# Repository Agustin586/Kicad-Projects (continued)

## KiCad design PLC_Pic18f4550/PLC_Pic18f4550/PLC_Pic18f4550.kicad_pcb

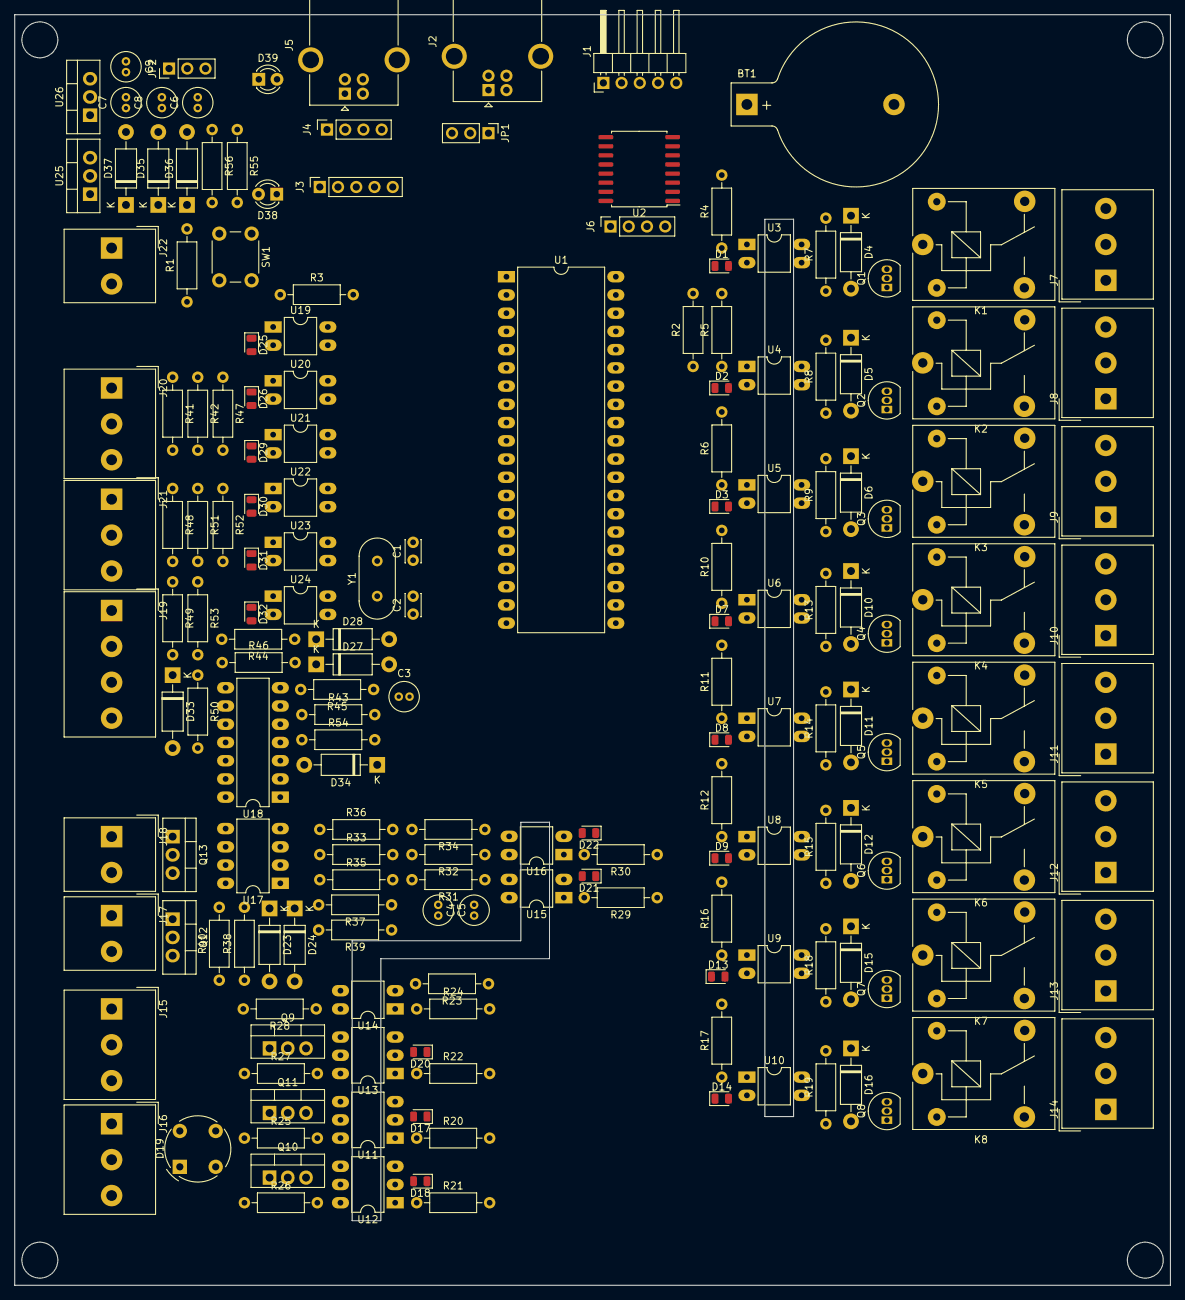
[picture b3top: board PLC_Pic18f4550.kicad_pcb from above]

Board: 2 copper layers, 161.0 x 177.0 mm, 178 parts (0 on the bottom side), 166 nets, no tracks yet.

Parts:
BT1: Battery_Cell; BatteryHolder_Keystone_103_1x20mm
C1, C2: C; C_Disc_D3.0mm_W2.0mm_P2.50mm
C3, C4, C5, C6, C7, C8, C9: C; C_Radial_D4.0mm_H7.0mm_P1.50mm
D1, D2, D3, D7, D8, D9, D13, D14, D17, D18, D20, D21, D22, D25, D26, D29, D30, D31, D32: LED; LED_0805_2012Metric
D4, D5, D6, D10, D11, D12, D15, D16, D23, D24, D35, D36, D37: 1N4007; D_DO-41_SOD81_P10.16mm_Horizontal
D19: D_Bridge_+A-A; Diode_Bridge_Round_D9.0mm
D27, D28, D33, D34: 1N47xxA; D_DO-41_SOD81_P10.16mm_Horizontal
D38, D39: LED; LED_D3.0mm
J1: Conn_01x05_Male; PinHeader_1x05_P2.54mm_Horizontal
J2, J5: USB_B; USB_B_OST_USB-B1HSxx_Horizontal
J3: Conn_01x05_Female; PinSocket_1x05_P2.54mm_Vertical
J4: Conn_01x04_Female; PinSocket_1x04_P2.54mm_Vertical
J6: Lcd_I2C; PinSocket_1x04_P2.54mm_Vertical
J7: SalidaRele0; Altech_AK300_1x03_P5.00mm_45-Degree
J8: SalidaRele1; Altech_AK300_1x03_P5.00mm_45-Degree
J9: SalidaRele2; Altech_AK300_1x03_P5.00mm_45-Degree
J10: SalidaRele3; Altech_AK300_1x03_P5.00mm_45-Degree
J11: SalidaRele4; Altech_AK300_1x03_P5.00mm_45-Degree
J12: SalidaRele5; Altech_AK300_1x03_P5.00mm_45-Degree
J13: SalidaRele6; Altech_AK300_1x03_P5.00mm_45-Degree
J14, J15, J16, J20, J21: Screw_Terminal_01x03; Altech_AK300_1x03_P5.00mm_45-Degree
J17, J18, J22: Screw_Terminal_01x02; Altech_AK300_1x02_P5.00mm_45-Degree
J19: Screw_Terminal_01x04; Altech_AK300_1x04_P5.00mm_45-Degree
JP1, JP2: Jumper_3_Bridged12; PinHeader_1x03_P2.54mm_Vertical
K1: Relay0; Relay_SPDT_SANYOU_SRD_Series_Form_C
K2: Relay1; Relay_SPDT_SANYOU_SRD_Series_Form_C
K3: Relay2; Relay_SPDT_SANYOU_SRD_Series_Form_C
K4: Relay3; Relay_SPDT_SANYOU_SRD_Series_Form_C
K5: Relay4; Relay_SPDT_SANYOU_SRD_Series_Form_C
K6: Relay5; Relay_SPDT_SANYOU_SRD_Series_Form_C
K7: Relay7; Relay_SPDT_SANYOU_SRD_Series_Form_C
K8: Relay8; Relay_SPDT_SANYOU_SRD_Series_Form_C
Q1, Q2, Q3, Q4, Q5, Q6, Q7, Q8: BC548; TO-92_Inline
Q9, Q10, Q11: BT136-500; TO-220-3_Vertical
Q12, Q13: IRF540N; TO-220-3_Vertical
R1, R2, R3, R4, R5, R6, R7, R8, R9, R10, R11, R12, R13, R14, R15, R16, R17, R18, R19, R20, R21, R22, R23, R24, R25, R26, R27, R28, R29, R30, R31, R32, R33, R34, R35, R36, R37, R38, R39, R40, R41, R42, R43, R44, R45, R46, R47, R48, R49, R50, R51, R52, R53, R54, R55, R56: R; R_Axial_DIN0207_L6.3mm_D2.5mm_P10.16mm_Horizontal
SW1: SW_Push; SW_PUSH_6mm
U1: PIC18F4550-IP; DIP-40_W15.24mm_LongPads
U2: DS3231M; SOIC-16W_7.5x10.3mm_P1.27mm
U3, U4, U5, U6, U7, U8, U9, U10, U14, U15, U16, U19, U20, U21, U22, U23, U24: PC817; DIP-4_W7.62mm_LongPads
U11, U12, U13: MOC3021M; DIP-6_W7.62mm_LongPads
U17: LM358; DIP-8_W7.62mm_LongPads
U18: LM324A; DIP-14_W7.62mm_LongPads
U25: LM7805_TO220; TO-220-3_Vertical
U26: LM7810_TO220; TO-220-3_Vertical
Y1: Crystal; Crystal_HC18-U_Vertical

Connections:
+5V: D4.1, D5.1, D6.1, D10.1, D11.1, D12.1, D15.1, D16.1, J1.2, J3.5, J6.3, JP2.2, K1.5, K2.5, K3.5, K4.5, K5.5, K6.5, K7.5, K8.5, R1.1, R2.1, R3.1, R28.2, R55.1, U1.11, U1.32, U2.2, U3.4, U4.4, U5.4, U6.4, U7.4, U8.4, U9.4, U10.4, U15.4, U16.4, U19.4, U20.4, U21.4, U22.4, U23.4, U24.4
+10V: C9.1, D23.1, D24.1, R56.1, U18.4, U26.3
+24V: D35.2, D36.2, J22.1, U17.8
/Control/OSC1: C1.1, U1.13, Y1.2
/Control/OSC2: C2.1, U1.14, Y1.1
/Control/RC4: J2.2, U1.23
/Control/RC5: J2.3, U1.24
/Control/RESET: JP1.2, U1.1
/Entradas/A0: J19.1, U18.3
/Entradas/A1: J19.2, U18.5
/Entradas/A2: J19.3, U18.10
/Entradas/A3: J19.4, U18.12
/Entradas/I0: J20.1, R41.2
/Entradas/I1: J20.2, R42.2
/Entradas/I2: J20.3, R47.2
/Entradas/I3: J21.1, R48.2
/Entradas/I4: J21.2, R51.2
/Entradas/I5: J21.3, R52.2
/Salidas/Salida_Reles/Rele1/Relay0: J7.1, K1.3
/Salidas/Salida_Reles/Rele1/Relay1: J7.3, K2.3
/Salidas/Salida_Reles/Rele1/Relay2: J8.2, K3.3
/Salidas/Salida_Reles/Rele1/Relay3: J9.1, K4.3
/Salidas/Salida_Reles/Rele1/Relay4: J10.1, K5.3
/Salidas/Salida_Reles/Rele1/Relay5: J10.3, K6.3
/Salidas/Salida_Reles/Rele1/Relay6: J11.2, K8.3
/Salidas/Salida_Reles/Rele1/Relay7: J12.1, K7.3
/Salidas/Salidas_Mosfet/Salida_Mosfet1: J17.1, Q12.3, R39.2
/Salidas/Salidas_Mosfet/Salida_Mosfet2: J18.1, Q13.3, R40.2
/Salidas/Salidas_Triac/Triac0: J15.1, Q10.1
/Salidas/Salidas_Triac/Triac1: J15.3, Q11.1
/Salidas/Salidas_Triac/Triac2: J16.2, Q9.1
CxC: R28.1, U1.35, U14.4
GND: BT1.2, C1.2, C2.2, C3.1, C4.1, C5.1, C6.2, C7.2, C8.2, C9.2, D1.1, D2.1, D3.1, D7.1, D8.1, D9.1, D13.1, D14.1, D17.1, D18.1, D20.1, D21.1, D22.1, D25.1, D26.1, D27.2, D28.2, D29.1, D30.1, D31.1, D32.1, D33.2, D34.2, D38.1, D39.1, J1.3, J2.4, J3.4, J6.4, J17.2, J18.2, J22.2, Q1.3, Q2.3, Q3.3, Q4.3, Q5.3, Q6.3, Q7.3, Q8.3, R33.1, R34.1, R45.1, R46.1, R53.1, R54.1, SW1.1, U1.12, U1.31, U2.5, U2.6, U2.7, U2.8, U2.9, U2.10, U2.11, U2.12, U2.13, U14.3, U17.4, U18.11, U25.2, U26.2
I0.0: U1.37, U19.3
I0.1: U1.38, U20.3
I0.2: J1.5, U1.39, U21.3
I0.3: J1.4, U1.40, U22.3
I0.4: U1.6, U23.3
I0.5: U1.7, U24.3
IA0.0: D27.1, R43.1, R45.2, U1.2
IA0.1: D28.1, R44.1, R46.2, U1.3
IA0.2: D33.1, R49.1, R53.2, U1.4
IA0.3: D34.1, R50.1, R54.2, U1.5
LineaAC1: D19.2, J14.1, K1.1, K2.1, K3.1, K4.1, Q9.2, Q10.2, Q11.2, R25.1, R26.1, R27.1
LineaAC2: D19.4, J7.2, J8.1, J8.3, J9.2, J14.3, J15.2, J16.1, J16.3
LineaDC1: J13.1, K5.1, K6.1, K7.1, K8.1
LineaDC2: J10.2, J11.1, J11.3, J12.2, J13.3
unnamed: BT1.1, U2.14
unnamed: C3.2, U1.18
unnamed: C4.2, R31.2, U17.3
unnamed: C5.2, R32.2, U17.5
unnamed: C6.1, D35.1, D37.1, U25.1
unnamed: C7.1, D36.1, U26.1
unnamed: C8.1, D37.2, JP2.1, U25.3
unnamed: D1.2, U3.2
unnamed: D2.2, U4.2
unnamed: D3.2, U5.2
unnamed: D4.2, K1.2, Q1.1
unnamed: D5.2, K2.2, Q2.1
unnamed: D6.2, K3.2, Q3.1
unnamed: D7.2, U6.2
unnamed: D8.2, U7.2
unnamed: D9.2, U8.2
unnamed: D10.2, K4.2, Q4.1
unnamed: D11.2, K5.2, Q5.1
unnamed: D12.2, K6.2, Q6.1
unnamed: D13.2, U9.2
unnamed: D14.2, U10.2
unnamed: D15.2, K7.2, Q7.1
unnamed: D16.2, K8.2, Q8.1
unnamed: D17.2, U11.2
unnamed: D18.2, U12.2
unnamed: D19.1, R23.2
unnamed: D19.3, U14.2
unnamed: D20.2, U13.2
unnamed: D21.2, U15.2
unnamed: D22.2, U16.2
unnamed: D23.2, Q12.2
unnamed: D24.2, Q13.2
unnamed: D25.2, U19.2
unnamed: D26.2, U20.2
unnamed: D29.2, U21.2
unnamed: D30.2, U22.2
unnamed: D31.2, U23.2
unnamed: D32.2, U24.2
unnamed: D38.2, R55.2
unnamed: D39.2, R56.2
unnamed: J1.1, JP1.1
unnamed: J4.1, J5.4
unnamed: J4.2, J5.3
unnamed: J4.3, J5.2
unnamed: J4.4, J5.1
unnamed: JP1.3, R1.2, SW1.2
unnamed: Q1.2, R7.1
unnamed: Q2.2, R8.1
unnamed: Q3.2, R9.1
unnamed: Q4.2, R13.1
unnamed: Q5.2, R14.1
unnamed: Q6.2, R15.1
unnamed: Q7.2, R18.1
unnamed: Q8.2, R19.1
unnamed: Q9.3, U11.4
unnamed: Q10.3, U12.4
unnamed: Q11.3, U13.4
unnamed: Q12.1, R37.1, R39.1
unnamed: Q13.1, R38.1, R40.1
unnamed: R4.1, U3.1
unnamed: R5.1, U4.1
unnamed: R6.1, U5.1
unnamed: R7.2, U3.3
unnamed: R8.2, U4.3
unnamed: R9.2, U5.3
unnamed: R10.1, U6.1
unnamed: R11.1, U7.1
unnamed: R12.1, U8.1
unnamed: R13.2, U6.3
unnamed: R14.2, U7.3
unnamed: R15.2, U8.3
unnamed: R16.1, U9.1
unnamed: R17.1, U10.1
unnamed: R18.2, U9.3
unnamed: R19.2, U10.3
unnamed: R20.1, U11.1
unnamed: R21.1, U12.1
unnamed: R22.1, U13.1
unnamed: R23.1, R24.2
unnamed: R24.1, U14.1
unnamed: R25.2, U11.6
unnamed: R26.2, U12.6
unnamed: R27.2, U13.6
unnamed: R29.2, U15.1
unnamed: R30.2, U16.1
unnamed: R31.1, U15.3
unnamed: R32.1, U16.3
unnamed: R33.2, R35.2, U17.2
unnamed: R34.2, R36.2, U17.6
unnamed: R35.1, R37.2, U17.1
unnamed: R36.1, R38.2, U17.7
unnamed: R41.1, U19.1
unnamed: R42.1, U20.1
unnamed: R43.2, U18.1, U18.2
unnamed: R44.2, U18.6, U18.7
unnamed: R47.1, U21.1
unnamed: R48.1, U22.1
unnamed: R49.2, U18.8, U18.9
unnamed: R50.2, U18.13, U18.14
unnamed: R51.1, U23.1
unnamed: R52.1, U24.1
Q0.0: R4.2, U1.19
Q0.1: R5.2, U1.20
Q0.2: R6.2, U1.21
Q0.3: R10.2, U1.22
Q0.4: R11.2, U1.27
Q0.5: R12.2, U1.28
Q0.6: R16.2, U1.29
Q0.7: R17.2, U1.30
Q1.0: R21.2, U1.8
Q1.1: R22.2, U1.9
Q1.2: R20.2, U1.10
Q1.3: R29.1, U1.16
Q1.4: R30.1, U1.17
RX: J3.2, U1.26
SCL: J6.1, R3.2, U1.34, U2.16
SDA: J6.2, R2.2, U1.33, U2.15
TX: J3.3, U1.25
VUSB: J2.1, JP2.3

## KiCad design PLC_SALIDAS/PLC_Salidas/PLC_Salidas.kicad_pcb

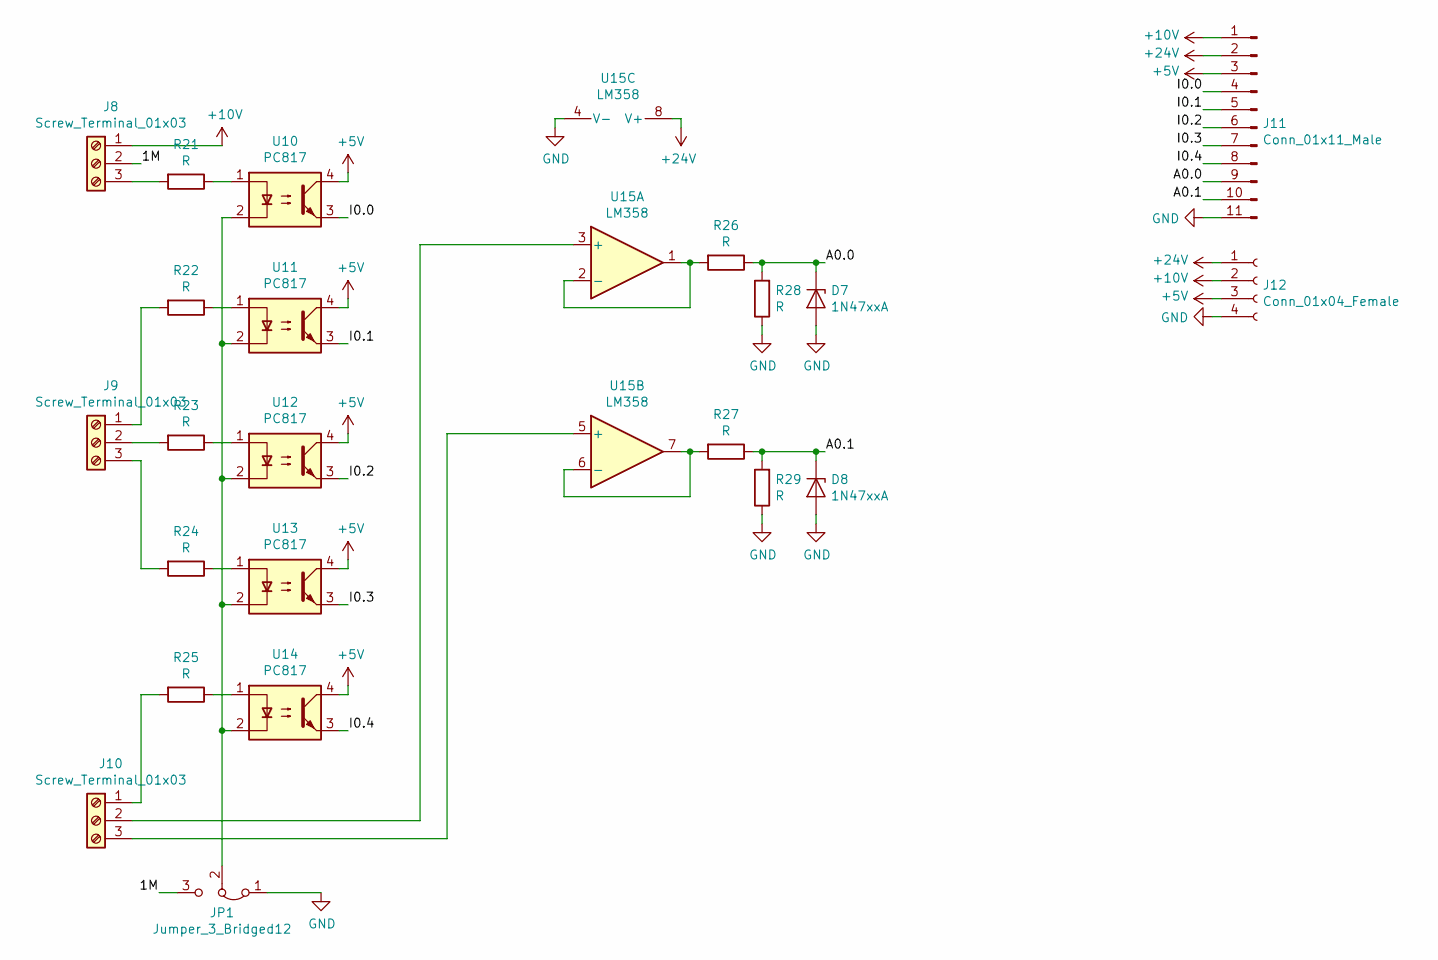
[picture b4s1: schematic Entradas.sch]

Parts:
D7, D8: 1N47xxA; D_DO-41_SOD81_P10.16mm_Horizontal
J8, J9, J10: Screw_Terminal_01x03; TerminalBlock_Phoenix_PT-1,5-3-5.0-H_1x03_P5.00mm_Horizontal
J11: Conn_01x11_Male; PinHeader_1x11_P2.54mm_Vertical
J12: Conn_01x04_Female; PinSocket_1x04_P2.54mm_Vertical
JP1: Jumper_3_Bridged12; PinHeader_1x03_P2.54mm_Vertical
R21, R22, R23, R24, R25, R26, R27, R28, R29: R; R_Axial_DIN0207_L6.3mm_D2.5mm_P10.16mm_Horizontal
U10, U11, U12, U13, U14: PC817; DIP-4_W7.62mm
U15: LM358; DIP-8_W7.62mm_LongPads

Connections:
+5V: J11.3, J12.3, U10.4, U11.4, U12.4, U13.4, U14.4; also elsewhere on the board
+10V: J8.1, J11.1, J12.2
+24V: J11.2, J12.1, U15.8 (V+)
/Entradas/1M: J8.2, JP1.3 (B)
/Entradas/A0.0: D7.1 (K), J11.9, R26.1, R28.2
/Entradas/A0.1: D8.1 (K), J11.10, R27.1, R29.2
/Entradas/I0.0: J11.4, U10.3
/Entradas/I0.1: J11.5, U11.3
/Entradas/I0.2: J11.6, U12.3
/Entradas/I0.3: J11.7, U13.3
/Entradas/I0.4: J11.8, U14.3
GND: D7.2 (A), D8.2 (A), J11.11, J12.4, JP1.1 (A), R28.1, R29.1, U15.4 (V-); also elsewhere on the board
unnamed: J8.3, R21.2
unnamed: J9.1, R22.2
unnamed: J9.2, R23.2
unnamed: J9.3, R24.2
unnamed: J10.1, R25.2
unnamed: J10.2, U15.3 (+)
unnamed: J10.3, U15.5 (+)
unnamed: JP1.2 (C), U10.2, U11.2, U12.2, U13.2, U14.2
unnamed: R21.1, U10.1
unnamed: R22.1, U11.1
unnamed: R23.1, U12.1
unnamed: R24.1, U13.1
unnamed: R25.1, U14.1
unnamed: R26.2, U15.1, U15.2 (-)
unnamed: R27.2, U15.6 (-), U15.7

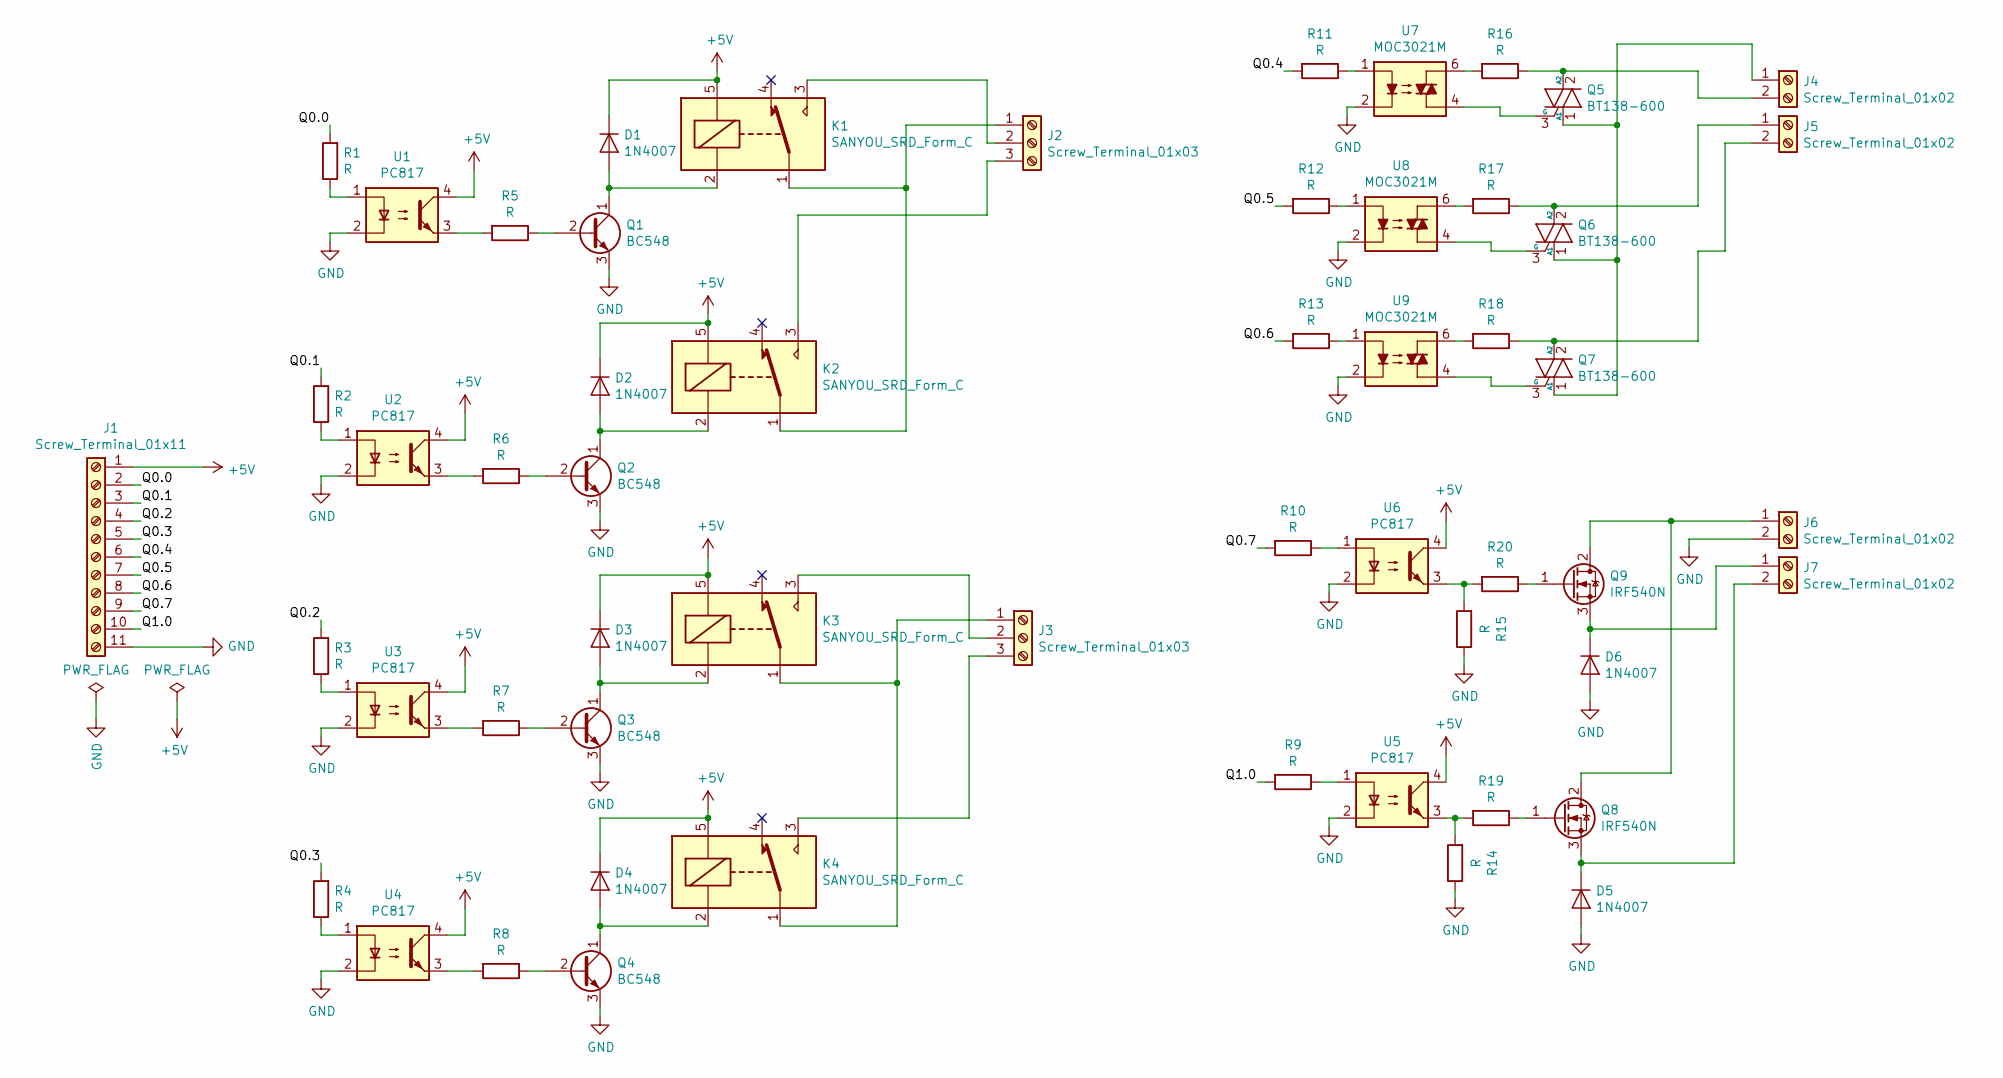
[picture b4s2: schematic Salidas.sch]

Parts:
D1, D2, D3, D4, D5, D6: 1N4007; D_DO-41_SOD81_P10.16mm_Horizontal
J1: Screw_Terminal_01x11; PinHeader_1x11_P2.54mm_Vertical
J2, J3: Screw_Terminal_01x03; TerminalBlock_Phoenix_PT-1,5-3-5.0-H_1x03_P5.00mm_Horizontal
J4, J5, J6, J7: Screw_Terminal_01x02; TerminalBlock_Phoenix_PT-1,5-2-5.0-H_1x02_P5.00mm_Horizontal
K1, K2, K3, K4: SANYOU_SRD_Form_C; Relay_SPDT_SANYOU_SRD_Series_Form_C
Q1, Q2, Q3, Q4: BC548; TO-92_Inline_Wide
Q5, Q6, Q7: BT138-600; TO-220-3_Vertical
Q8, Q9: IRF540N; TO-220-3_Vertical
R1, R2, R3, R4, R5, R6, R7, R8, R9, R10, R11, R12, R13, R14, R15, R16, R17, R18, R19, R20: R; R_Axial_DIN0207_L6.3mm_D2.5mm_P10.16mm_Horizontal
U1, U2, U3, U4: PC817; DIP-4_W7.62mm_LongPads
U5, U6: PC817; DIP-4_W7.62mm
U7, U8, U9: MOC3021M; DIP-6_W7.62mm_LongPads

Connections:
+5V: D1.1 (K), D2.1 (K), D3.1 (K), D4.1 (K), J1.1, K1.5, K2.5, K3.5, K4.5, U1.4, U2.4, U3.4, U4.4, U5.4, U6.4; also elsewhere on the board
/Salidas/Q0.0: J1.2, R1.2
/Salidas/Q0.1: J1.3, R2.2
/Salidas/Q0.2: J1.4, R3.2
/Salidas/Q0.3: J1.5, R4.2
/Salidas/Q0.4: J1.6, R11.2
/Salidas/Q0.5: J1.7, R12.2
/Salidas/Q0.6: J1.8, R13.2
/Salidas/Q0.7: J1.9, R10.2
/Salidas/Q1.0: J1.10, R9.2
GND: D5.2 (A), D6.2 (A), J1.11, J6.2, Q1.3 (E), Q2.3 (E), Q3.3 (E), Q4.3 (E), R14.1, R15.1, U1.2, U2.2, U3.2, U4.2, U5.2, U6.2, U7.2, U8.2, U9.2; also elsewhere on the board
unnamed: D1.2 (A), K1.2, Q1.1 (C)
unnamed: D2.2 (A), K2.2, Q2.1 (C)
unnamed: D3.2 (A), K3.2, Q3.1 (C)
unnamed: D4.2 (A), K4.2, Q4.1 (C)
unnamed: D5.1 (K), J7.2, Q8.3 (S)
unnamed 26: D6.1 (K), J7.1, Q9.3 (S); also elsewhere on the board
unnamed: J2.1, K1.1, K2.1
unnamed: J2.2, K1.3
unnamed: J2.3, K2.3
unnamed: J3.1, K3.1, K4.1
unnamed: J3.2, K3.3
unnamed: J3.3, K4.3
unnamed: J4.1, Q5.1 (A1), Q6.1 (A1), Q7.1 (A1)
unnamed: J4.2, Q5.2 (A2), R16.1
unnamed: J5.1, Q6.2 (A2), R17.1
unnamed: J5.2, Q7.2 (A2), R18.1
unnamed: J6.1, Q8.2 (D), Q9.2 (D)
unnamed: Q1.2 (B), R5.1
unnamed: Q2.2 (B), R6.1
unnamed: Q3.2 (B), R7.1
unnamed: Q4.2 (B), R8.1
unnamed: Q5.3 (G), U7.4
unnamed: Q6.3 (G), U8.4
unnamed: Q7.3 (G), U9.4
unnamed: Q8.1 (G), R19.1
unnamed: Q9.1 (G), R20.1
unnamed: R1.1, U1.1
unnamed: R2.1, U2.1
unnamed: R3.1, U3.1
unnamed: R4.1, U4.1
unnamed: R5.2, U1.3
unnamed: R6.2, U2.3
unnamed: R7.2, U3.3
unnamed: R8.2, U4.3
unnamed: R9.1, U5.1
unnamed: R10.1, U6.1
unnamed: R11.1, U7.1
unnamed: R12.1, U8.1
unnamed: R13.1, U9.1
unnamed: R14.2, R19.2, U5.3
unnamed: R15.2, R20.2, U6.3
unnamed: R16.2, U7.6
unnamed: R17.2, U8.6
unnamed: R18.2, U9.6

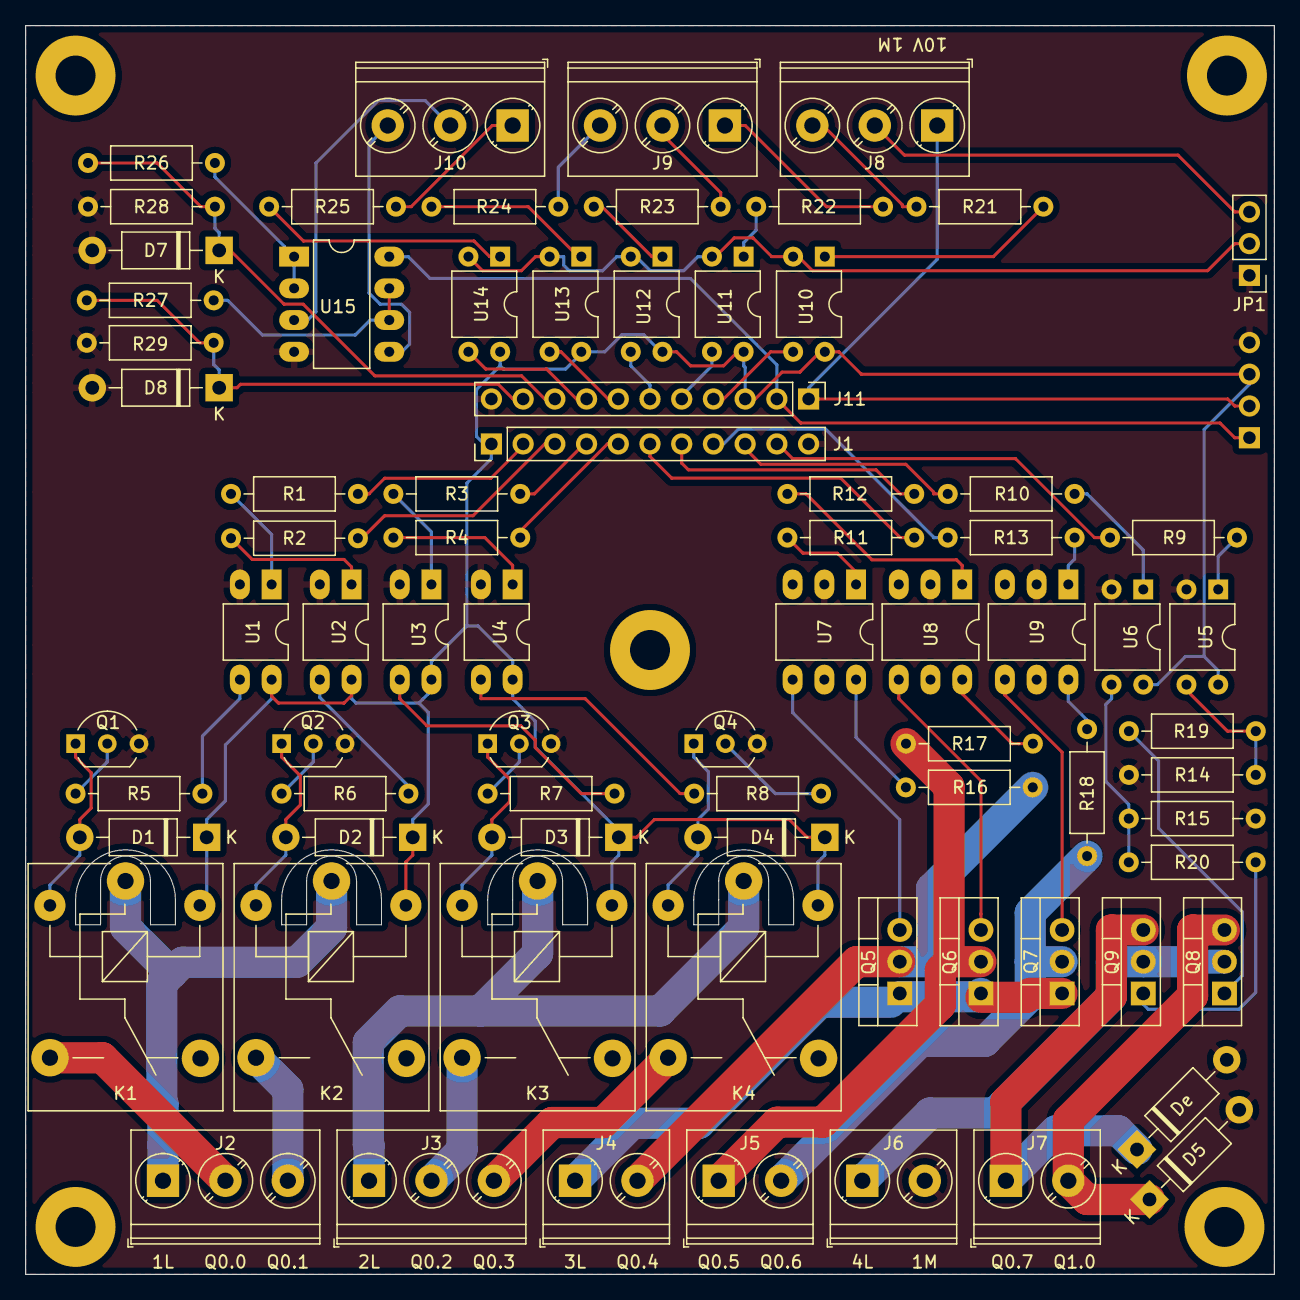
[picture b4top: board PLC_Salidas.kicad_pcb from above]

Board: 2 copper layers, 100.0 x 100.0 mm, 83 parts (1 on the bottom side), 80 nets.

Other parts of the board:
De: 1N4007; D_DO-41_SOD81_P10.16mm_Horizontal
REF1, REF1#2, REF2, REF3, REF4: MountingHole_3.2mm_M3_Pad

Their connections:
GND: De.2; also elsewhere on the board
unnamed 26: De.1; also elsewhere on the board
